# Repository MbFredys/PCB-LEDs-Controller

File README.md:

# LED Controller — Earlier Design Exercise

Earlier PCB design exercise combining an ESP32, AC/DC supply modules and LED-control circuitry.

> **Status: unvalidated design exercise.** KiCad files, a PDF schematic and renders are available. No firmware or test results are supplied. The published manufacturing directory contains drill-related files, not a complete released fabrication package.

## Intended architecture

The published component netlist includes:

- **ESP32-WROOM-32** controller.
- **IRM-60-12** and **IRM-60-24** AC/DC supply modules.
- **PCA9685BS** PWM controller.
- **FT232RL** USB-to-UART interface.
- **MOC3021M** optocoupler and **BT136-500** triac.
- **2N7000** devices and **LM1117-3.3** regulation.

The supply-module ratings are component ratings, not validated output capabilities of the assembled board. Scheduling, wireless control, efficiency improvements and dimming performance require firmware and testing and are not demonstrated here.

## Before further development

1. Review mains-related separation, protection, component ratings and enclosure requirements.
2. Verify low-voltage rail loading, signal levels and the proposed LED drive stages.
3. Define load types, channel currents, switching behavior and fault handling.
4. Run ERC/DRC after synchronizing schematic and PCB.
5. Prepare a complete reviewed BOM and fabrication package.
6. Develop firmware and validate a prototype using appropriate safety procedures.

Do not connect the board to mains or send the historical outputs for production based only on this documentation.

## Relationship to later work

The separate [RGB+CCT controller](https://github.com/MbFredys/RGB-LED-and-High-Dencity-CCT-Controller) explores a five-channel architecture with a nominal 12 V input. It is also a design under review, not a validated replacement product.

## Files

| Directory | Purpose |
|---|---|
| [KiCAD files](KiCAD%20files/) | Editable schematic, PCB, project, BOM and netlist |
| [PDF Schematic](PDF%20Schematic/) | PDF circuit documentation |
| [Release](Release/) | Renders |
| [Manufacturing](Manufacturing/) | Partial historical outputs |
| [Firmware](Firmware/) | Availability note; no implementation |

## License

CERN-OHL-W-2.0. See [LICENSE](LICENSE) and [COPYING](COPYING).

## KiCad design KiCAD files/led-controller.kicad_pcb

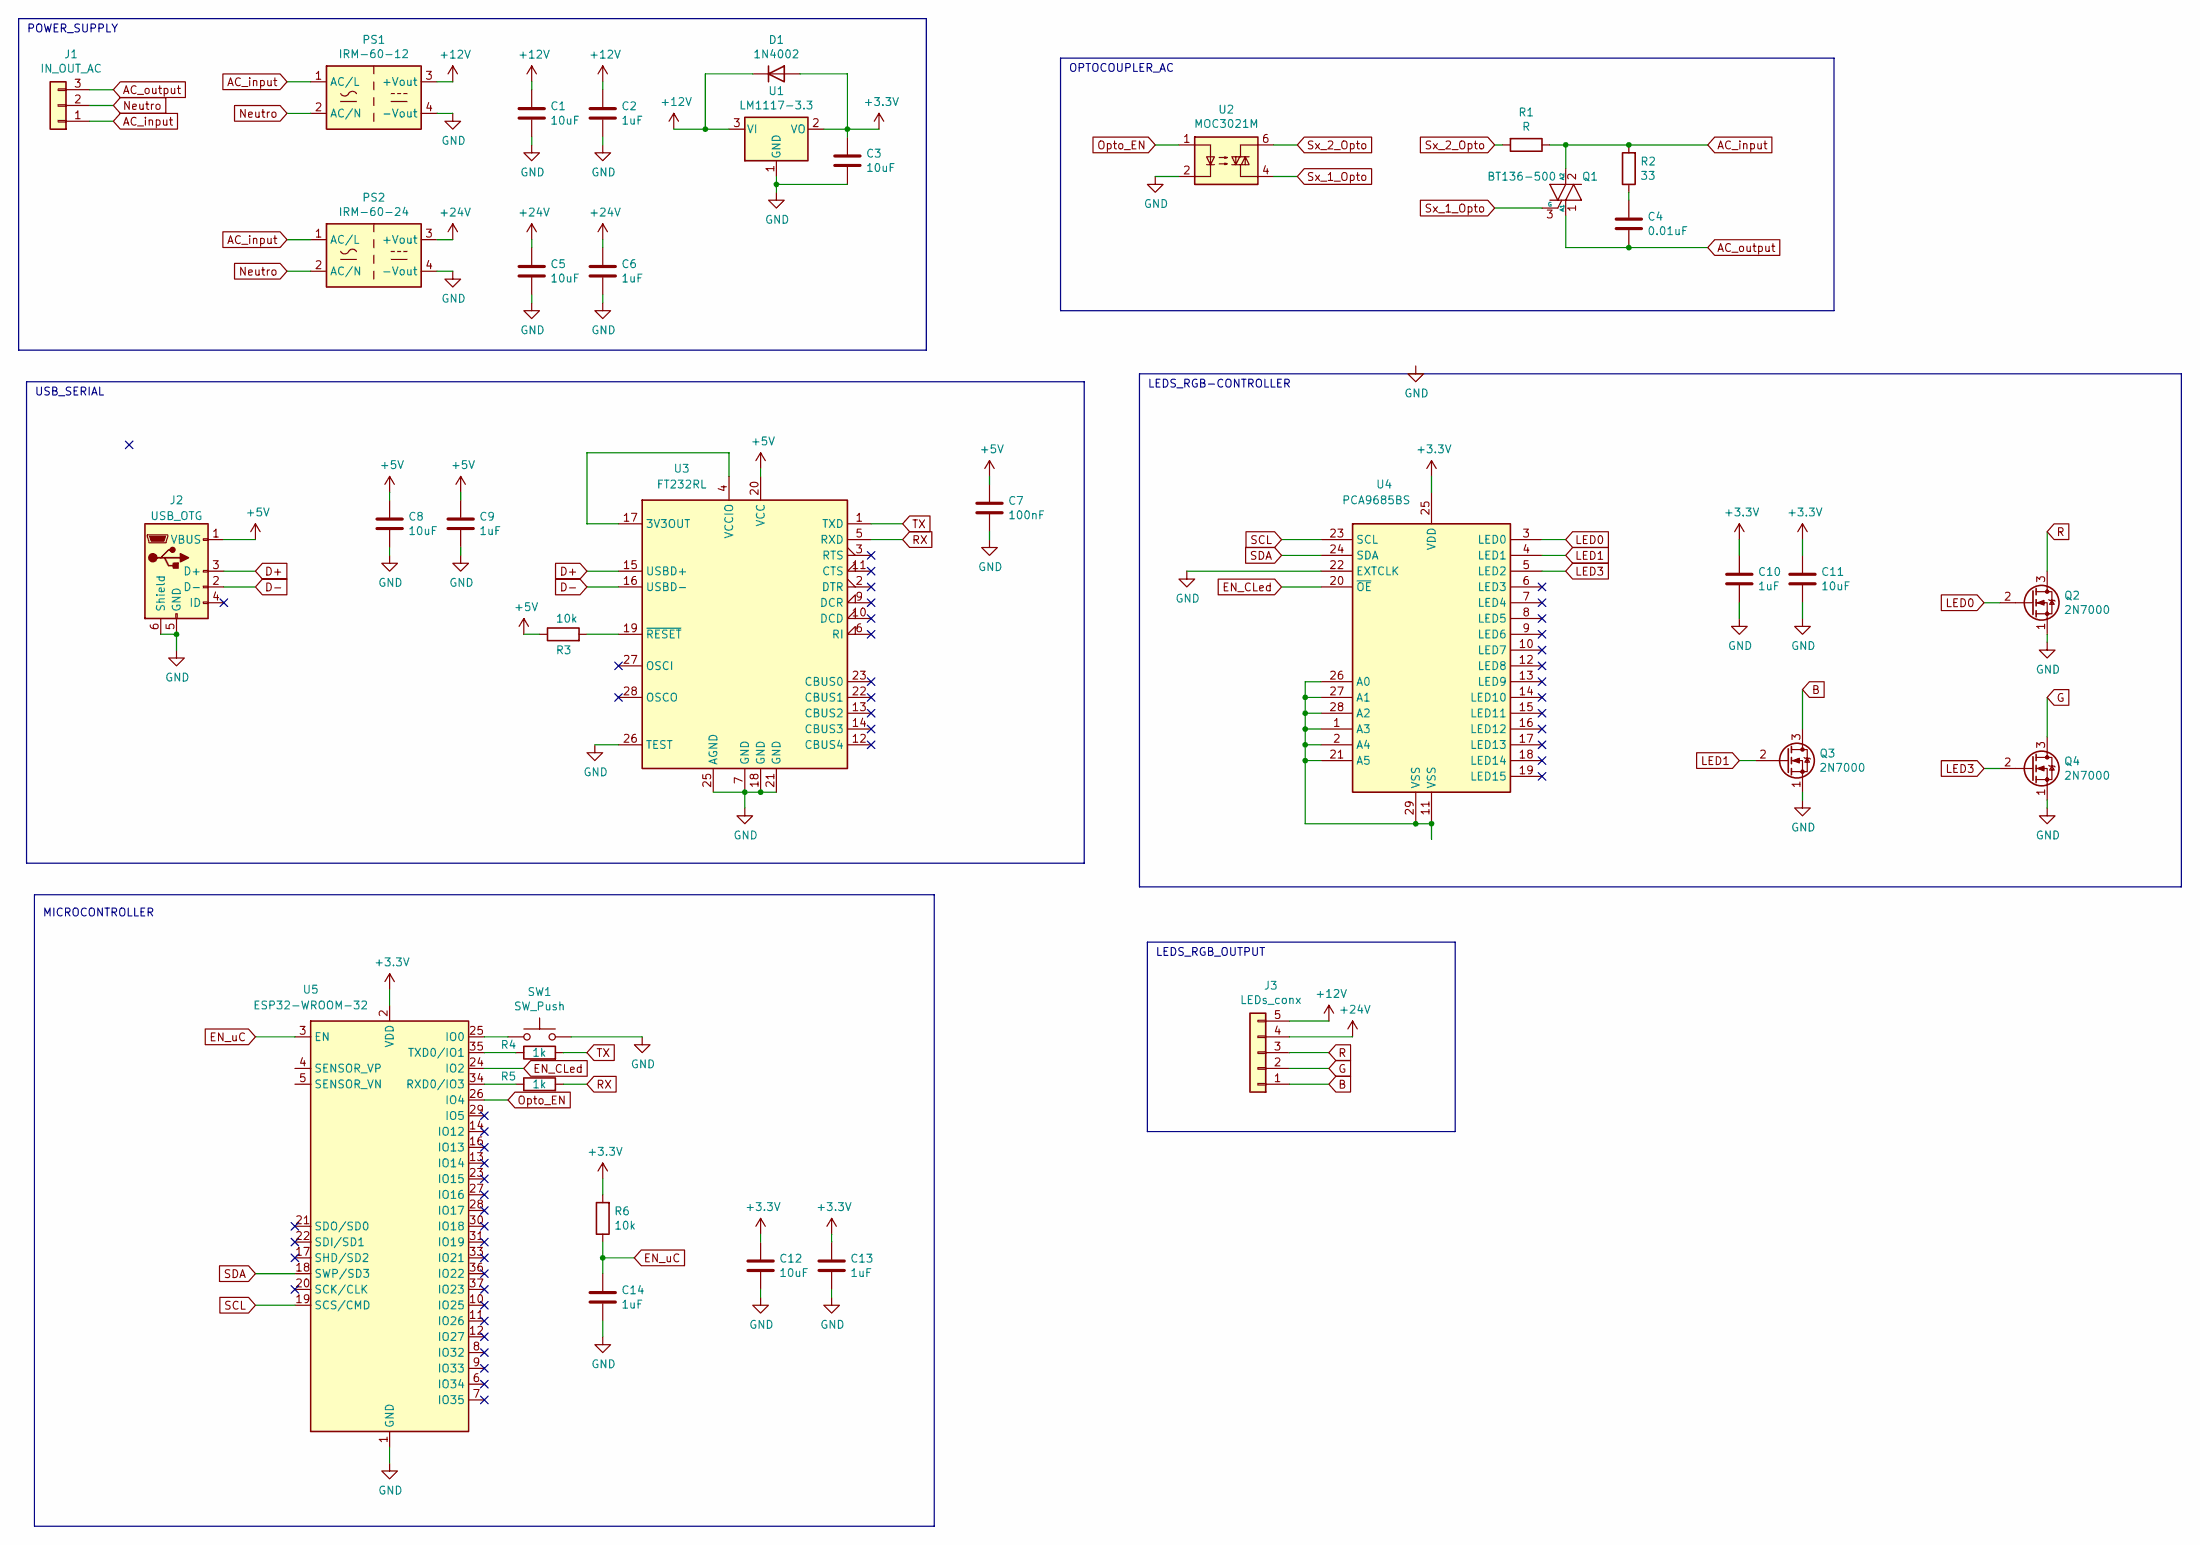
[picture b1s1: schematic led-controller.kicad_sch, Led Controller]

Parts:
C1, C3, C5, C8, C11, C12: 10uF; CP_Elec_5x5.4
C2, C6, C9, C10, C13, C14: 1uF; CP_Elec_5x5.4
C4: 0.01uF; C_1210_3225Metric_Pad1.33x2.70mm_HandSolder
C7: 100nF; C_1210_3225Metric_Pad1.33x2.70mm_HandSolder
D1: 1N4002; D_PowerDI-123
J1: IN_OUT_AC; TerminalBlock_Phoenix_PT-1,5-3-5.0-H_1x03_P5.00mm_Horizontal
J2: USB_OTG; USB_Micro-B_Molex_47346-0001
J3: LEDs_conx; TerminalBlock_Phoenix_MPT-0,5-5-2.54_1x05_P2.54mm_Horizontal
PS1: IRM-60-12; Converter_ACDC_MeanWell_IRM-60-xx_THT_new
PS2: IRM-60-24; Converter_ACDC_MeanWell_IRM-60-xx_THT_new
Q1: BT136-500; TO-220-3_Vertical
Q2, Q3, Q4: 2N7000; SOT-89-3_Handsoldering
R1: R; R_0805_2012Metric_Pad1.20x1.40mm_HandSolder
R2: 33; R_0805_2012Metric_Pad1.20x1.40mm_HandSolder
R3, R6: 10k; R_1206_3216Metric_Pad1.30x1.75mm_HandSolder
R4, R5: 1k; R_1206_3216Metric_Pad1.30x1.75mm_HandSolder
SW1: SW_Push; SW_SPST_B3U-1000P
U1: LM1117-3.3; SOT-223-3_TabPin2
U2: MOC3021M; DIP762W45P254L889H508Q6_NEW
U3: FT232RL; SSOP-28_5.3x10.2mm_P0.65mm
U4: PCA9685BS; QFN-28-1EP_6x6mm_P0.65mm_EP4.25x4.25mm
U5: ESP32-WROOM-32

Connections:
+3V3: C3.1, C10.1, C11.1, C12.1, C13.1, D1.2 (A), R6.2, U1.2 (VO), U4.25 (VDD), U5.2 (VDD)
+5V: C7.1, C8.1, C9.1, J2.1 (VBUS), R3.1, U3.20 (VCC)
+12V: C1.1, C2.1, D1.1 (K), J3.5, PS1.3 (+Vout), U1.3 (VI)
+24V: C5.1, C6.1, J3.4, PS2.3 (+Vout)
AC_input: J1.1, PS1.1 (AC/L), PS2.1 (AC/L), Q1.2 (A2), R1.1, R2.2
AC_output: C4.2, J1.3, Q1.1 (A1)
B: J3.1, Q3.3 (D)
D+: J2.3 (D+), U3.15 (USBD+)
D-: J2.2 (D-), U3.16 (USBD-)
EN_CLed: U4.20 (~OE), U5.24 (IO2)
EN_uC: C14.1, R6.1, U5.3 (EN)
G: J3.2, Q4.3 (D)
GND: C1.2, C2.2, C3.2, C5.2, C6.2, C7.2, C8.2, C9.2, C10.2, C11.2, C12.2, C13.2, C14.2, J2.5 (GND), J2.6 (Shield), PS1.4 (-Vout), PS2.4 (-Vout), Q2.1 (S), Q3.1 (S), Q4.1 (S), SW1.2, U1.1 (GND), U2.2, U3.7 (GND), U3.18 (GND), U3.21 (GND), U3.25 (AGND), U3.26 (TEST), U4.22 (EXTCLK), U5.1 (GND), U5.15 (GND), U5.38 (GND), U5.39 (GND)
LED0: Q2.2 (G), U4.3 (LED0)
LED1: Q3.2 (G), U4.4 (LED1)
LED3: Q4.2 (G), U4.5 (LED2)
unnamed: C4.1, R2.1
unnamed: U3.4 (VCCIO), U3.17 (3V3OUT)
unnamed: R3.2, U3.19 (~RESET)
unnamed: U4.1 (A3), U4.2 (A4), U4.11 (VSS), U4.21 (A5), U4.26 (A0), U4.27 (A1), U4.28 (A2), U4.29 (VSS)
unnamed: SW1.1, U5.25 (IO0)
unnamed: R5.1, U5.34 (RXD0/IO3)
unnamed: R4.1, U5.35 (TXD0/IO1)
Neutro: J1.2, PS1.2 (AC/N), PS2.2 (AC/N)
Opto_EN: U2.1, U5.26 (IO4)
R: J3.3, Q2.3 (D)
RX: R5.2, U3.5 (RXD)
SCL: U4.23 (SCL), U5.19 (SCS/CMD)
SDA: U4.24 (SDA), U5.18 (SWP/SD3)
Sx_1_Opto: Q1.3 (G), U2.4
Sx_2_Opto: R1.2, U2.6
TX: R4.2, U3.1 (TXD)

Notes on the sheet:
MICROCONTROLLER
LEDS_RGB_OUTPUT
POWER_SUPPLY
USB_SERIAL
LEDS_RGB-CONTROLLER
OPTOCOUPLER_AC

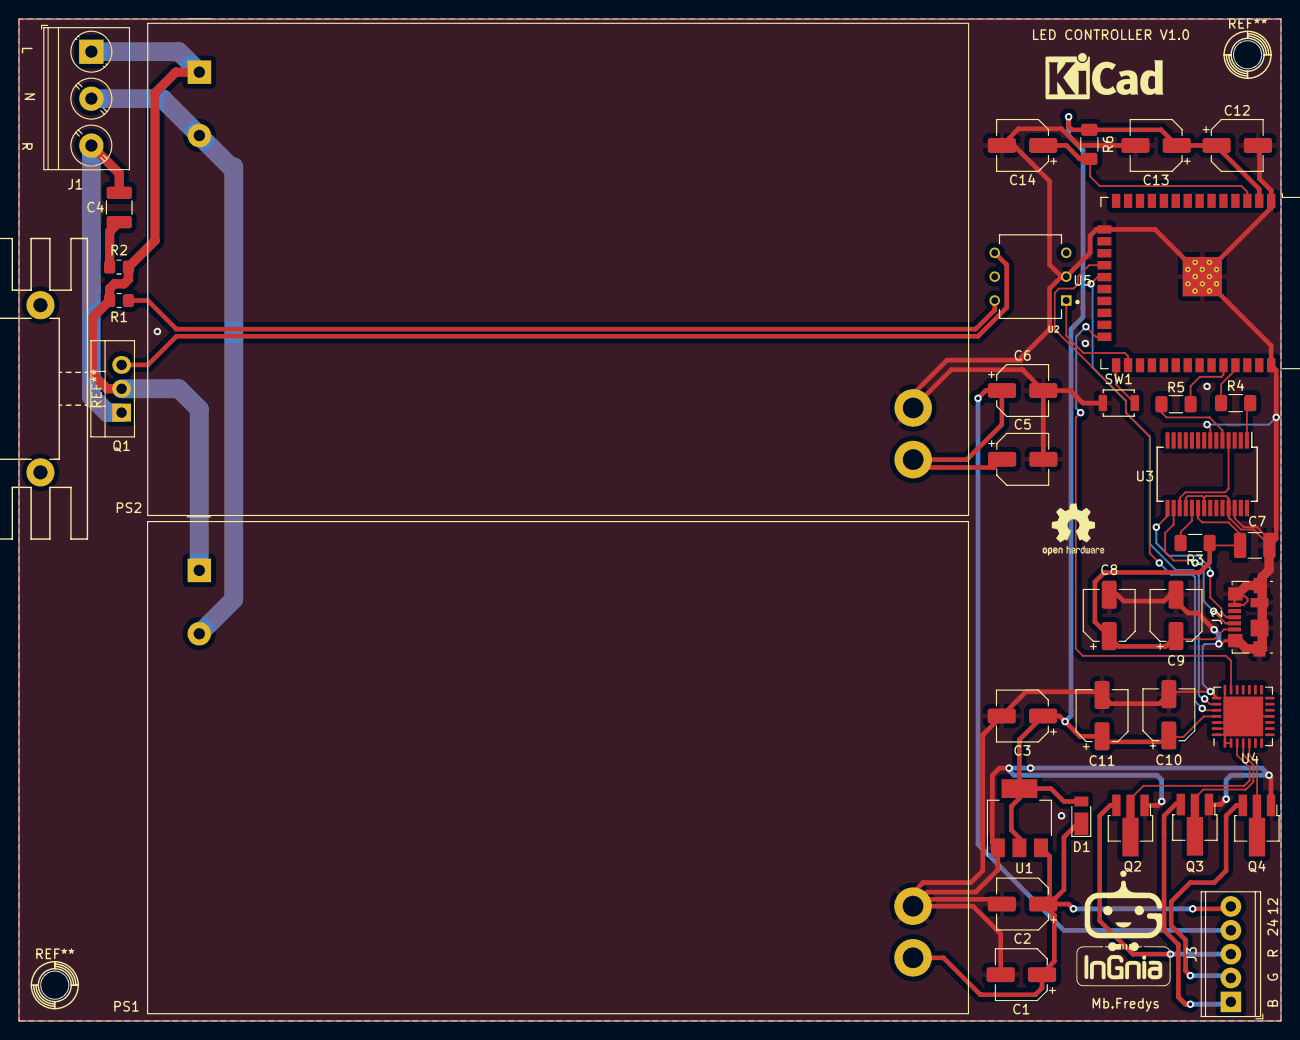
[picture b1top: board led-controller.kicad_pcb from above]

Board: 2 copper layers, 134.4 x 106.7 mm, 36 parts (0 on the bottom side), 32 nets.

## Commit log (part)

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2023-07-16 Agregando archivos al repositorio
2025-12-01 Change license to CERN Open Hardware Licence v2
    Updated the license from MIT to CERN Open Hardware Licence Version 2.
2025-12-01 Add CERN Open Hardware Licence Version 2
    This file contains the CERN Open Hardware Licence Version 2 - Weakly Reciprocal, detailing terms for use, modification, and distribution of covered source and products.
2025-12-01 Change license from MIT to CERN-OHL-W-2.0
    Updated the license information to reflect CERN-OHL-W-2.0.
2025-12-01 Fix license URL in LICENSE file
    Updated the link to the CERN-OHL-W v2 license.
